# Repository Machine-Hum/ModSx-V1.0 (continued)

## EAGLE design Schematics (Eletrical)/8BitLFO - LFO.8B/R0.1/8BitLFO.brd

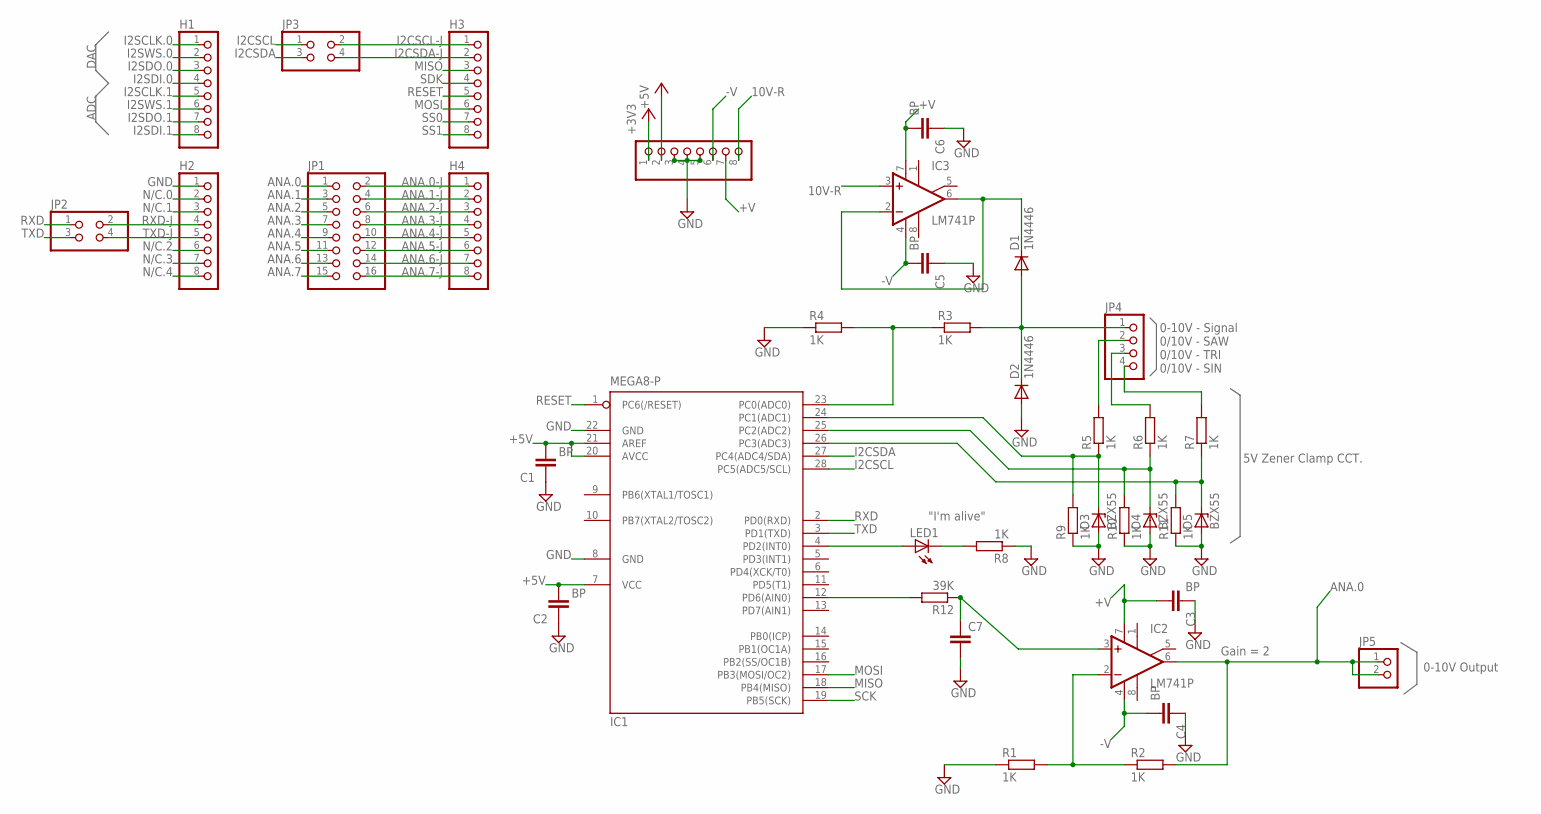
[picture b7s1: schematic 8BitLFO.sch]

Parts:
C1, C2, C3, C4, C5, C6: BP; C0.1PTH
C7: C7.5/3; C7.5B3
D1, D2: 1N4446; DO35-10
D3, D4, D5: BZX55; DO35Z10
H1, H2, H3, H4, H5: PINHD-1X8; 1X08
IC1: MEGA8-P; DIL28-3
IC2, IC3: LM741P; DIL08
JP1: PINHD-2X8; 2X08
JP2, JP3: PINHD-2X2; 2X02
JP4: PINHD-1X4/90; 1X04/90
JP5: PINHD-1X2/90; 1X02/90
LED1: LED-5MM
R1, R2, R3, R4, R5, R6, R7, R8, R9, R10, R11: 1K; RTH025W
R12: 39K; RTH025W

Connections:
10V-R: H5.8, IC3.3 (+IN)
+3V3: H5.1
+5V: C1.1, C2.1, H5.2, IC1.7 (VCC), IC1.20 (AVCC), IC1.21 (AREF)
+V: C3.1, C6.1, H5.7, IC2.7 (V+), IC3.7 (V+)
-V: C4.1, C5.1, H5.6, IC2.4 (V-), IC3.4 (V-)
ANA.0: IC2.6 (OUT), JP1.1, JP5.1, JP5.2, R2.2
ANA.0-J: H4.1, JP1.2
ANA.1: JP1.3
ANA.1-J: H4.2, JP1.4
ANA.2: JP1.5
ANA.2-J: H4.3, JP1.6
ANA.3: JP1.7
ANA.3-J: H4.4, JP1.8
ANA.4: JP1.9
ANA.4-J: H4.5, JP1.10
ANA.5: JP1.11
ANA.5-J: H4.6, JP1.12
ANA.6: JP1.13
ANA.6-J: H4.7, JP1.14
ANA.7: JP1.15
ANA.7-J: H4.8, JP1.16
GND: C1.2, C2.2, C3.2, C4.2, C5.2, C6.2, C7.2, D2.A, D3.A, D4.A, D5.A, H2.1, H5.3, H5.4, H5.5, IC1.8 (GND), IC1.22 (GND), R1.1, R4.1, R8.1, R9.1, R10.1, R11.1
I2CSCL: IC1.28 (PC5(ADC5/SCL)), JP3.1
I2CSCL-J: H3.1, JP3.2
I2CSDA: IC1.27 (PC4(ADC4/SDA)), JP3.3
I2CSDA-J: H3.2, JP3.4
I2SCLK.0: H1.1
I2SCLK.1: H1.5
I2SDI.0: H1.4
I2SDI.1: H1.8
I2SDO.0: H1.3
I2SDO.1: H1.7
I2SWS.0: H1.2
I2SWS.1: H1.6
MISO: H3.3, IC1.18 (PB4(MISO))
MOSI: H3.6, IC1.17 (PB3(MOSI/OC2))
unnamed: IC2.2 (-IN), R1.2, R2.1
unnamed: D1.C, IC3.2 (-IN), IC3.6 (OUT)
unnamed: IC1.12 (PD6(AIN0)), R12.2
unnamed: C7.1, IC2.3 (+IN), R12.1
unnamed: D1.A, D2.C, JP4.1, R3.2
unnamed: IC1.23 (PC0(ADC0)), R3.1, R4.2
unnamed: D3.C, IC1.24 (PC1(ADC1)), R5.1, R9.2
unnamed: D4.C, IC1.25 (PC2(ADC2)), R6.1, R10.2
unnamed: D5.C, IC1.26 (PC3(ADC3)), R7.1, R11.2
unnamed: JP4.2, R5.2
unnamed: JP4.3, R6.2
unnamed: JP4.4, R7.2
unnamed: IC1.4 (PD2(INT0)), LED1.A
unnamed: LED1.K (C), R8.2
N/C.0: H2.2
N/C.1: H2.3
N/C.2: H2.6
N/C.3: H2.7
N/C.4: H2.8
RESET: H3.5, IC1.1 (PC6(/RESET))
RXD: IC1.2 (PD0(RXD)), JP2.1
RXD-J: H2.4, JP2.2
SCK: H3.4, IC1.19 (PB5(SCK))
SS0: H3.7
SS1: H3.8
TXD: IC1.3 (PD1(TXD)), JP2.3
TXD-J: H2.5, JP2.4

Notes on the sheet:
10V-R
I2SCLK.0
I2SWS.0
I2SDO.0
I2SDI.0
I2SCLK.1
I2SWS.1
I2SDO.1
I2SDI.1
GND
N/C.0
RXD-J
TXD-J
N/C.1
N/C.2
N/C.3
N/C.4
I2CSCL
I2CSDA
MISO
SDK
RESET
MOSI
SS0
SS1
ANA.0-J
ANA.1-J
ANA.2-J
ANA.3-J
ANA.4-J
ANA.5-J
ANA.6-J
ANA.7-J
ANA.0
ANA.1
ANA.2
ANA.3
ANA.4
ANA.5
ANA.6

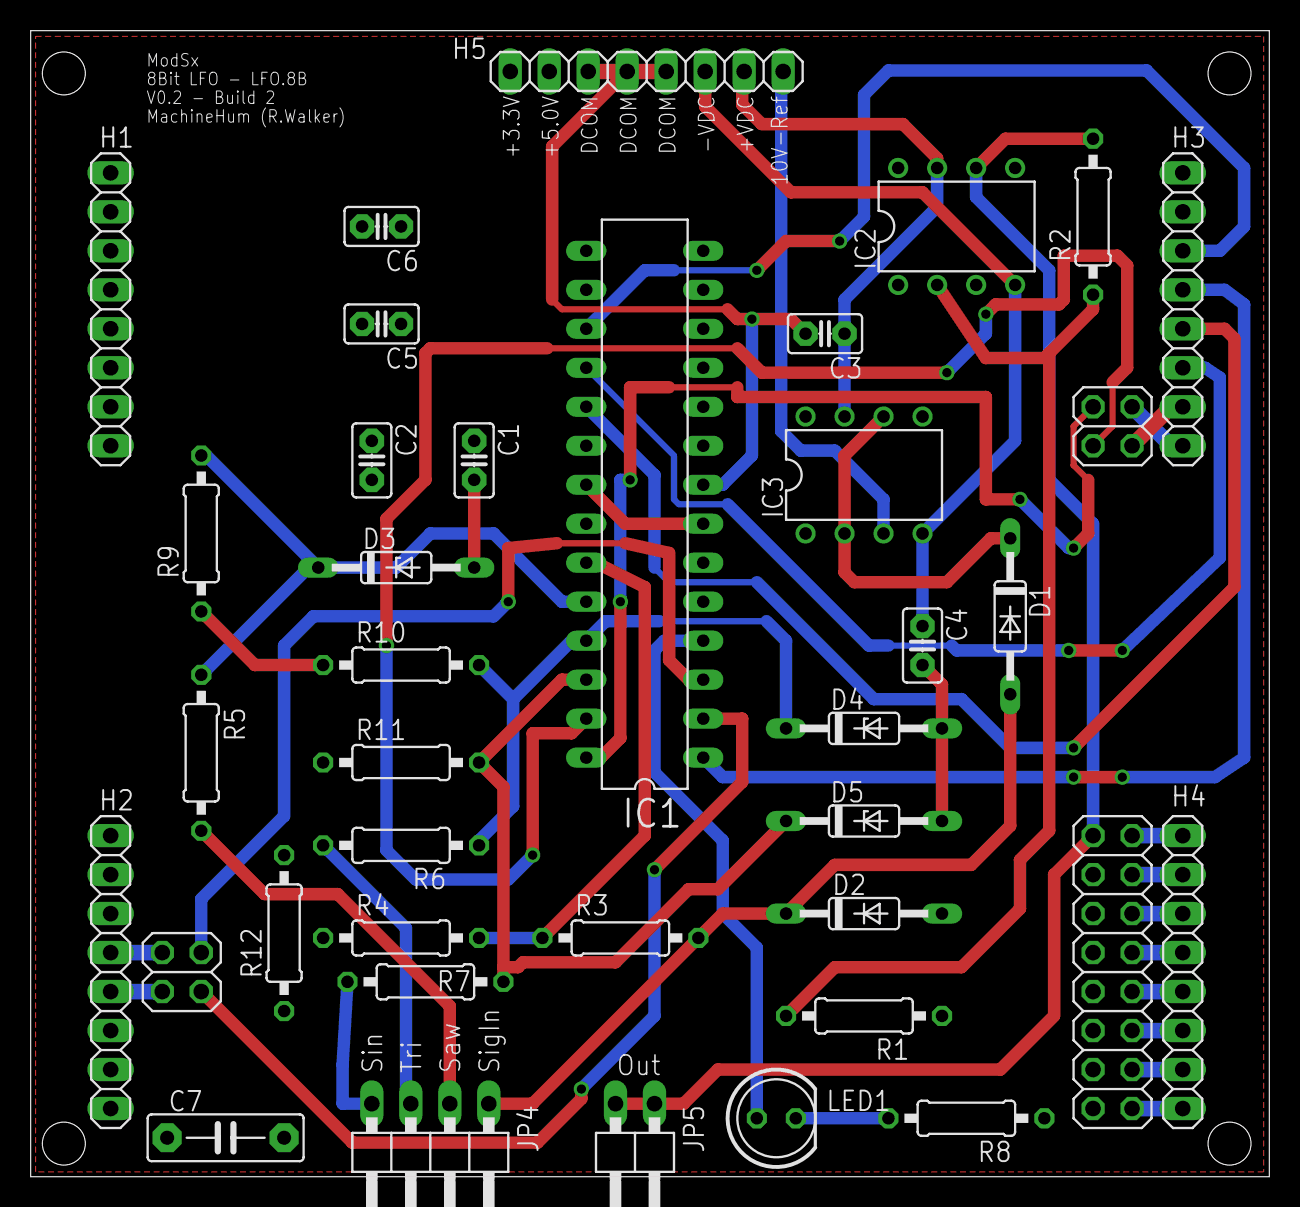
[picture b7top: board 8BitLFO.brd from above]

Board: 2 copper layers, 80.7 x 74.7 mm, 38 parts (0 on the bottom side), 40 nets.

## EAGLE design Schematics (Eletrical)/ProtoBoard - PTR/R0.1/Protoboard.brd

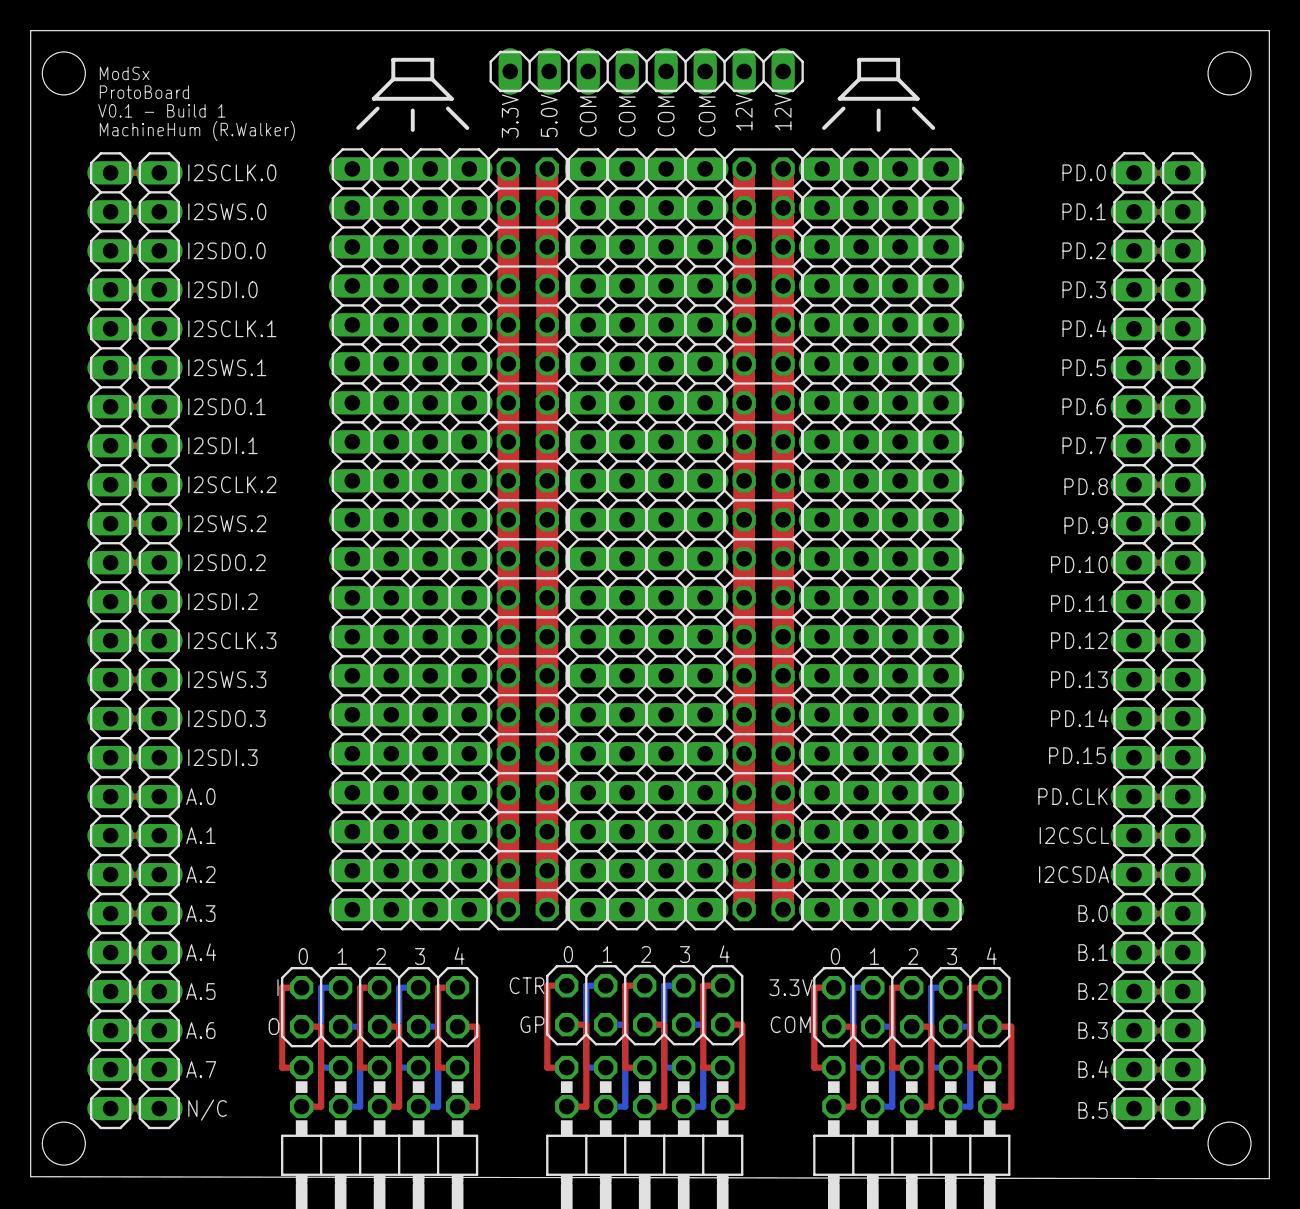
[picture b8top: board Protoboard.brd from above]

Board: 2 copper layers, 80.7 x 74.8 mm, 25 parts (0 on the bottom side), 145 nets.

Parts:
GYH, GYH1: 1X25
JP1, JP2: 1X25
JP3: 1X08
JP4, JP5, JP6: 2X05/90
JP7, JP8, JP9: 2X05
JP10, JP11, JP12, JP13, JP14, JP15, JP16, JP17, JP20, JP21, JP22, JP23: 1X20
JP18, JP19: 2X20

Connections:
unnamed: GYH.25, GYH1.1
unnamed: GYH.24, GYH1.2
unnamed: GYH.23, GYH1.3
unnamed: GYH.22, GYH1.4
unnamed: GYH.21, GYH1.5
unnamed: GYH.20, GYH1.6
unnamed: JP1.25, JP2.1
unnamed: JP1.24, JP2.2
unnamed: JP1.23, JP2.3
unnamed: JP1.22, JP2.4
unnamed: JP1.21, JP2.5
unnamed: JP1.19, JP2.7
unnamed: GYH.19, GYH1.7
unnamed: GYH.18, GYH1.8
unnamed: GYH.17, GYH1.9
unnamed: GYH.16, GYH1.10
unnamed: GYH.15, GYH1.11
unnamed: GYH.14, GYH1.12
unnamed: GYH.13, GYH1.13
unnamed: GYH.12, GYH1.14
unnamed: GYH.11, GYH1.15
unnamed: GYH.10, GYH1.16
unnamed: GYH.9, GYH1.17
unnamed: GYH.8, GYH1.18
unnamed: GYH.7, GYH1.19
unnamed: GYH.6, GYH1.20
unnamed: GYH.5, GYH1.21
unnamed: GYH.4, GYH1.22
unnamed: GYH.3, GYH1.23
unnamed: GYH.2, GYH1.24
unnamed: GYH.1, GYH1.25
unnamed: JP1.20, JP2.6
unnamed: JP1.18, JP2.8
unnamed: JP1.17, JP2.9
unnamed: JP1.16, JP2.10
unnamed: JP1.15, JP2.11
unnamed: JP1.14, JP2.12
unnamed: JP1.13, JP2.13
unnamed: JP1.12, JP2.14
unnamed: JP1.11, JP2.15
unnamed: JP1.10, JP2.16
unnamed: JP1.9, JP2.17
unnamed: JP1.8, JP2.18
unnamed: JP1.7, JP2.19
unnamed: JP1.6, JP2.20
unnamed: JP1.5, JP2.21
unnamed: JP1.4, JP2.22
unnamed: JP1.3, JP2.23
unnamed: JP1.2, JP2.24
unnamed: JP1.1, JP2.25
unnamed: JP4.1, JP7.1
unnamed: JP4.2, JP7.2
unnamed: JP4.3, JP7.3
unnamed: JP4.4, JP7.4
unnamed: JP4.5, JP7.5
unnamed: JP4.6, JP7.6
unnamed: JP4.7, JP7.7
unnamed: JP4.8, JP7.8
unnamed: JP4.9, JP7.9
unnamed: JP4.10, JP7.10
unnamed: JP5.1, JP8.1
unnamed: JP5.2, JP8.2
unnamed: JP5.3, JP8.3
unnamed: JP5.4, JP8.4
unnamed: JP5.5, JP8.5
unnamed: JP5.6, JP8.6
unnamed: JP5.7, JP8.7
unnamed: JP5.8, JP8.8
unnamed: JP5.9, JP8.9
unnamed: JP5.10, JP8.10
unnamed: JP6.1, JP9.1
unnamed: JP6.2, JP9.2
unnamed: JP6.3, JP9.3
unnamed: JP6.4, JP9.4
unnamed: JP6.5, JP9.5
unnamed: JP6.6, JP9.6
unnamed: JP6.7, JP9.7
unnamed: JP6.8, JP9.8
unnamed: JP6.9, JP9.9
unnamed: JP6.10, JP9.10
unnamed: JP10.1, JP11.20, JP12.1, JP13.1
unnamed: JP10.2, JP11.19, JP12.2, JP13.2
unnamed: JP10.3, JP11.18, JP12.3, JP13.3
unnamed: JP10.4, JP11.17, JP12.4, JP13.4
unnamed: JP10.5, JP11.16, JP12.5, JP13.5
unnamed: JP10.6, JP11.15, JP12.6, JP13.6
unnamed: JP10.7, JP11.14
unnamed: JP10.8, JP11.13, JP12.8, JP13.8
unnamed: JP10.9, JP11.12, JP12.9, JP13.9
unnamed: JP10.10, JP11.11, JP12.10, JP13.10
unnamed: JP10.11, JP11.10, JP12.11, JP13.11
unnamed: JP10.12, JP11.9, JP12.12, JP13.12
unnamed: JP10.13, JP11.8, JP12.13, JP13.13
unnamed: JP10.14, JP11.7, JP12.14, JP13.14
unnamed: JP10.15, JP11.6, JP12.15, JP13.15
unnamed: JP10.16, JP11.5, JP12.16, JP13.16
unnamed: JP10.17, JP11.4, JP12.17, JP13.17
unnamed: JP10.18, JP11.3, JP12.18, JP13.18
unnamed: JP10.19, JP11.2, JP12.19, JP13.19
unnamed: JP12.7, JP13.7
unnamed: JP14.1, JP15.20, JP16.1, JP17.1
unnamed: JP10.20, JP11.1, JP12.20, JP13.20
unnamed: JP14.2, JP15.19, JP16.2, JP17.2
unnamed: JP14.3, JP15.18, JP16.3, JP17.3
unnamed: JP14.4, JP15.17, JP16.4, JP17.4
unnamed: JP14.5, JP15.16, JP16.5, JP17.5
unnamed: JP14.6, JP15.15, JP16.6, JP17.6
unnamed: JP14.7, JP15.14, JP16.7, JP17.7
unnamed: JP14.8, JP15.13, JP16.8, JP17.8
unnamed: JP14.9, JP15.12, JP16.9, JP17.9
unnamed: JP14.10, JP15.11, JP16.10, JP17.10
unnamed: JP14.11, JP15.10, JP16.11, JP17.11
unnamed: JP14.12, JP15.9, JP16.12, JP17.12
unnamed: JP14.13, JP15.8, JP16.13, JP17.13
unnamed: JP14.14, JP15.7, JP16.14, JP17.14
unnamed: JP14.15, JP15.6, JP16.15, JP17.15
unnamed: JP14.16, JP15.5, JP16.16, JP17.16
unnamed: JP14.17, JP15.4, JP16.17, JP17.17
unnamed: JP14.18, JP15.3, JP16.18, JP17.18
unnamed: JP14.19, JP15.2, JP16.19, JP17.19
unnamed: JP14.20, JP15.1, JP16.20, JP17.20
unnamed: JP18.1, JP18.3, JP18.5, JP18.7, JP18.9, JP18.11, JP18.13, JP18.15, JP18.17, JP18.19, JP18.21, JP18.23, JP18.25, JP18.27, JP18.29, JP18.31, JP18.33, JP18.35, JP18.37, JP18.39
unnamed: JP18.2, JP18.4, JP18.6, JP18.8, JP18.10, JP18.12, JP18.14, JP18.16, JP18.18, JP18.20, JP18.22, JP18.24, JP18.26, JP18.28, JP18.30, JP18.32, JP18.34, JP18.36, JP18.38, JP18.40
unnamed: JP19.1, JP19.3, JP19.5, JP19.7, JP19.9, JP19.11, JP19.13, JP19.15, JP19.17, JP19.19, JP19.21, JP19.23, JP19.25, JP19.27, JP19.29, JP19.31, JP19.33, JP19.35, JP19.37, JP19.39
unnamed: JP19.2, JP19.4, JP19.6, JP19.8, JP19.10, JP19.12, JP19.14, JP19.16, JP19.18, JP19.20, JP19.22, JP19.24, JP19.26, JP19.28, JP19.30, JP19.32, JP19.34, JP19.36, JP19.38, JP19.40
unnamed: JP20.1, JP21.20, JP22.1, JP23.1
unnamed: JP20.2, JP21.19, JP22.2, JP23.2
unnamed: JP20.3, JP21.18, JP22.3, JP23.3
unnamed: JP20.4, JP21.17, JP22.4, JP23.4
unnamed: JP20.5, JP21.16, JP22.5, JP23.5
unnamed: JP20.6, JP21.15, JP22.6, JP23.6
unnamed: JP20.7, JP21.14, JP22.7, JP23.7
unnamed: JP20.8, JP21.13, JP22.8, JP23.8
unnamed: JP20.9, JP21.12, JP22.9, JP23.9
unnamed: JP20.10, JP21.11, JP22.10, JP23.10
unnamed: JP20.11, JP21.10, JP22.11, JP23.11
unnamed: JP20.12, JP21.9, JP22.12, JP23.12
unnamed: JP20.13, JP21.8, JP22.13, JP23.13
unnamed: JP20.14, JP21.7, JP22.14, JP23.14
unnamed: JP20.15, JP21.6, JP22.15, JP23.15
unnamed: JP20.16, JP21.5, JP22.16, JP23.16
unnamed: JP20.17, JP21.4, JP22.17, JP23.17
unnamed: JP20.18, JP21.3, JP22.18, JP23.18
unnamed: JP20.19, JP21.2, JP22.19, JP23.19
unnamed: JP20.20, JP21.1, JP22.20, JP23.20

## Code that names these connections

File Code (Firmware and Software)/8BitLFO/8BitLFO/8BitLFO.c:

/*
 * 8BitLFO.c
 *
 * Walker - LFO (Low Frequency Ossilator)
 * 1Hz - 20Hz
 *
 * Created: 5/14/2015 6:21:04 PM
 *  Author: Walker
 */ 

//31254 "Ticks" on 16Bit Counter w/ 256 Samples = 1Hz
//1563 "Ticks" on 16Bit Counter w/ 256 Samples = 20Hz

#include <avr/io.h>
#include <util/delay.h>
#include <avr/interrupt.h>
//#include <math.h>

#define PI 3.1415926
#define SIN 0
#define SAW 1
#define TRI 2
#define LED PD2

uint8_t SinW[256], WaveForm, Pointer;
uint16_t Tmr1;

//Funk Prototypes
void init(void);
void fill(void);
void set_8(uint8_t);
void set_16(uint16_t);
void delay(uint16_t);

ISR(TIMER1_COMPA_vect)
{
	cli(); // Don't do it
	
	TCNT1H = 0; //Kill the timer
	TCNT1L = 0;
	
	Pointer++; //Pointer up PLX
	
	//Saw Tooth
	if(WaveForm == SAW)
		set_8(Pointer);
	
	//Triangle
	else if(WaveForm == TRI) 
	{
		if(Pointer < 0x7F)
			set_8(Pointer*2);
		
		else if(Pointer > 0x7F)
			set_8((0xFF - Pointer)*2);
	}
	else //WaveForm == SIN
		set_8(SinW[Pointer]);
	
	
	//set_8(126);
		
	sei(); //Over
}

int main(void)
{
	Pointer = 0;
	
	cli(); //Disable interrupts for now plx
	
	init();
	fill();
	
	sei(); //Enable interrupts

	ADCSRA |= (1 << ADSC); //Start first Analog read

    while(1)
	{
		if((ADCSRA >> ADIF) & 1) //if there's a reading...
			{
				
				set_16((ADCH*(-119)) + 31254); //Set Deal
				ADCSRA |= (1 << ADIF); //READ THIS SCALEING THING
				
			}
			_delay_ms(10); // Let it tick a little
			
			if(~(PINC >> PC1) & 1)
				WaveForm = SAW;
			else if(~(PINC >> PC2) & 1)
				WaveForm = TRI;
			else
				WaveForm = SIN;
		//nop
	}
}

void init(void)
{
	DDRD |= (1 << PD6) | (1 << LED); // OC0A output	
	DDRC &= (0b11110000); // Lower 4 are inputs
	
	PORTC |= (0b00001110);
	
	//8Bit PWM stuff
	TCCR0A = 0b10000011; 
	TCCR0B = 0b00000001; //8Mhz
	
	//16Bit Interupt Source
	TCCR1A = 0b00000000;
	TCCR1B = 0b00000001; //8MHz Clock
	TIMSK1 = 0b00000010;

	//ADC
	ADMUX = 0b01100000;
	ADCSRA = 0b10100000; //Enable ADC | AutoTrigger
	ADCSRB &= 0b01000000; //FreeRunning
	DIDR0 |= (1 >> ADC0D);
	
	//NOW I'M ALIVE
	uint8_t dex = 100;
	
	while(dex != 0)
	{
		dex = (dex - 10);
		PORTD |= (1<<LED);
		delay(dex);
		PORTD &= ~(1<<LED);
		delay(dex);
	}
	
	PORTD |= (1<<LED);
}

void fill(void)
{
	double temp;
	Pointer = 0;
	
	temp = (2*PI)/256;
	
	do
	{
		SinW[Pointer] = (int) (((sin(temp*Pointer))*0x7f)+0x7f);
		Pointer++;
		
	}while(Pointer < 255);
	
	SinW[255] = 127; //Quick and Dirty
	
	Pointer = 0;
	//Not yet
}

//Set PWM DUC of output PD6 (0x00 to 0xFF)
void set_8(uint8_t data)
{
	OCR0A = data;
}

//Set PWM DUC of output PD6 (0x00 to 0xFF)
void set_16(uint16_t data)
{
	OCR1AH = ((data & 0xFF00) >> 8);
	OCR1AL = (data & 0x00FF);
}


void delay(uint16_t time_ms)
{
	while (time_ms != 0)
	{
		_delay_ms(1);
		time_ms--;
		
	}
	
}

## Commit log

2016-02-12 Feb 11th, 2016 -------------- Initial Release
2016-02-12 Feb 11th, 2016 -------------- Readme Update
2016-02-12 Feb 11th, 2016 -------------- Name Change
2016-02-12 Feb11th, 2016 ------------- -Added pictes -Changed Readme
